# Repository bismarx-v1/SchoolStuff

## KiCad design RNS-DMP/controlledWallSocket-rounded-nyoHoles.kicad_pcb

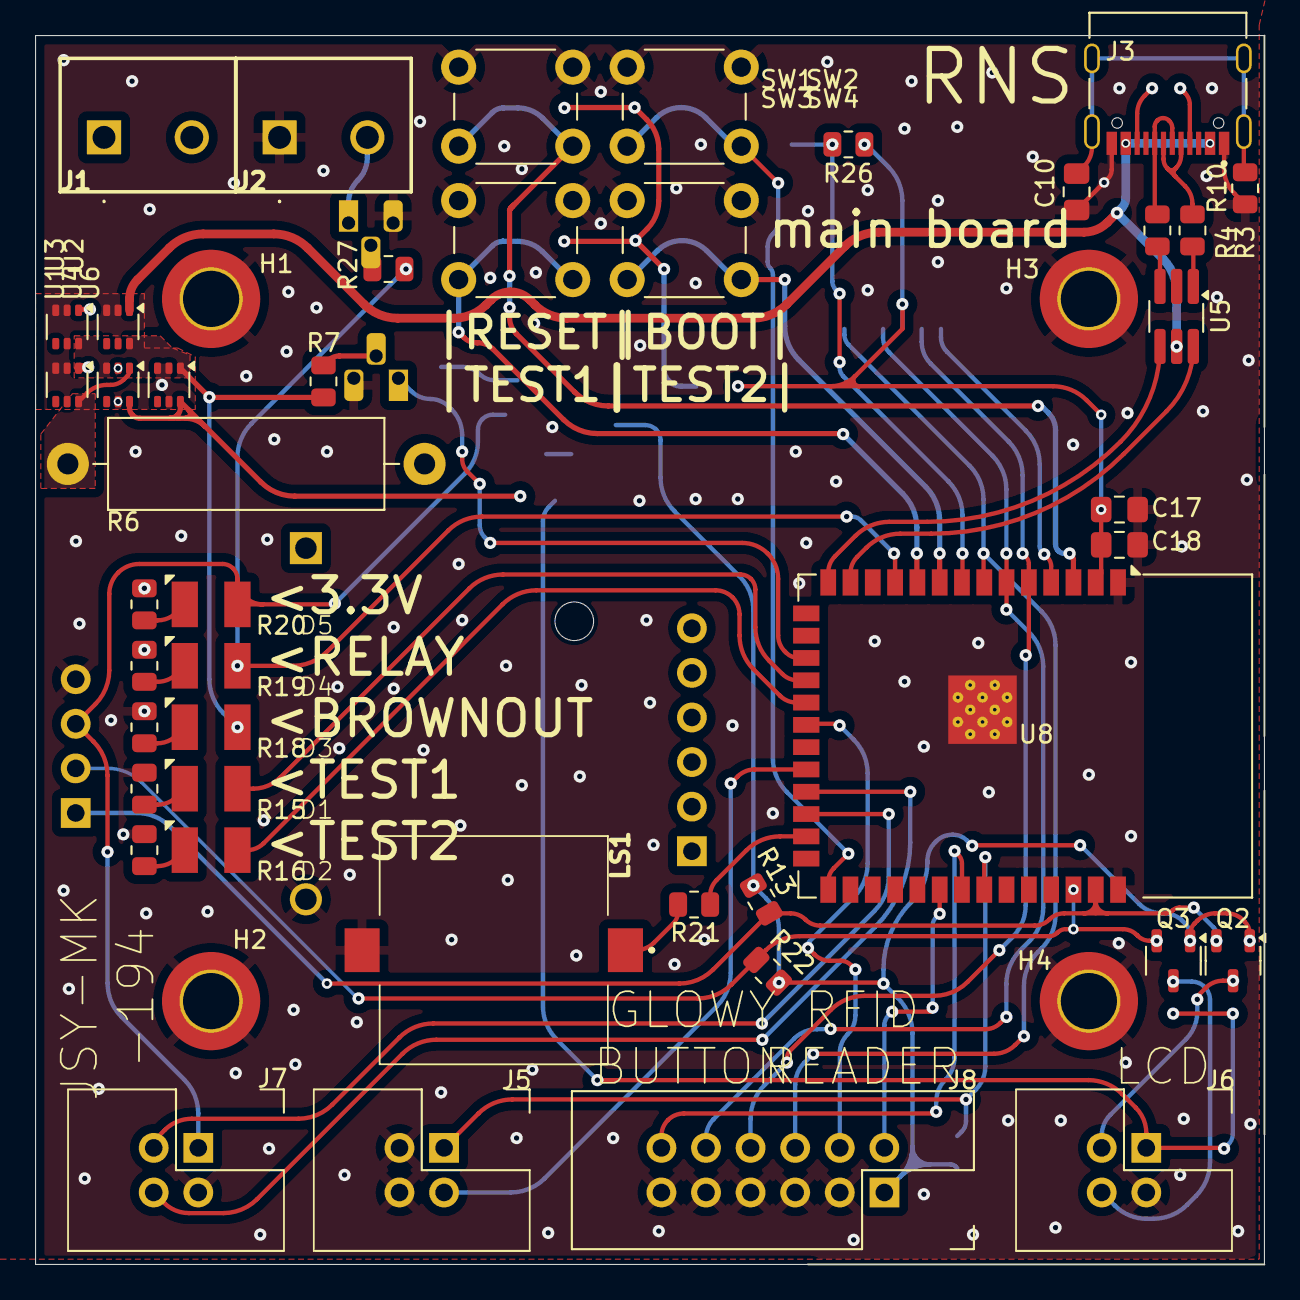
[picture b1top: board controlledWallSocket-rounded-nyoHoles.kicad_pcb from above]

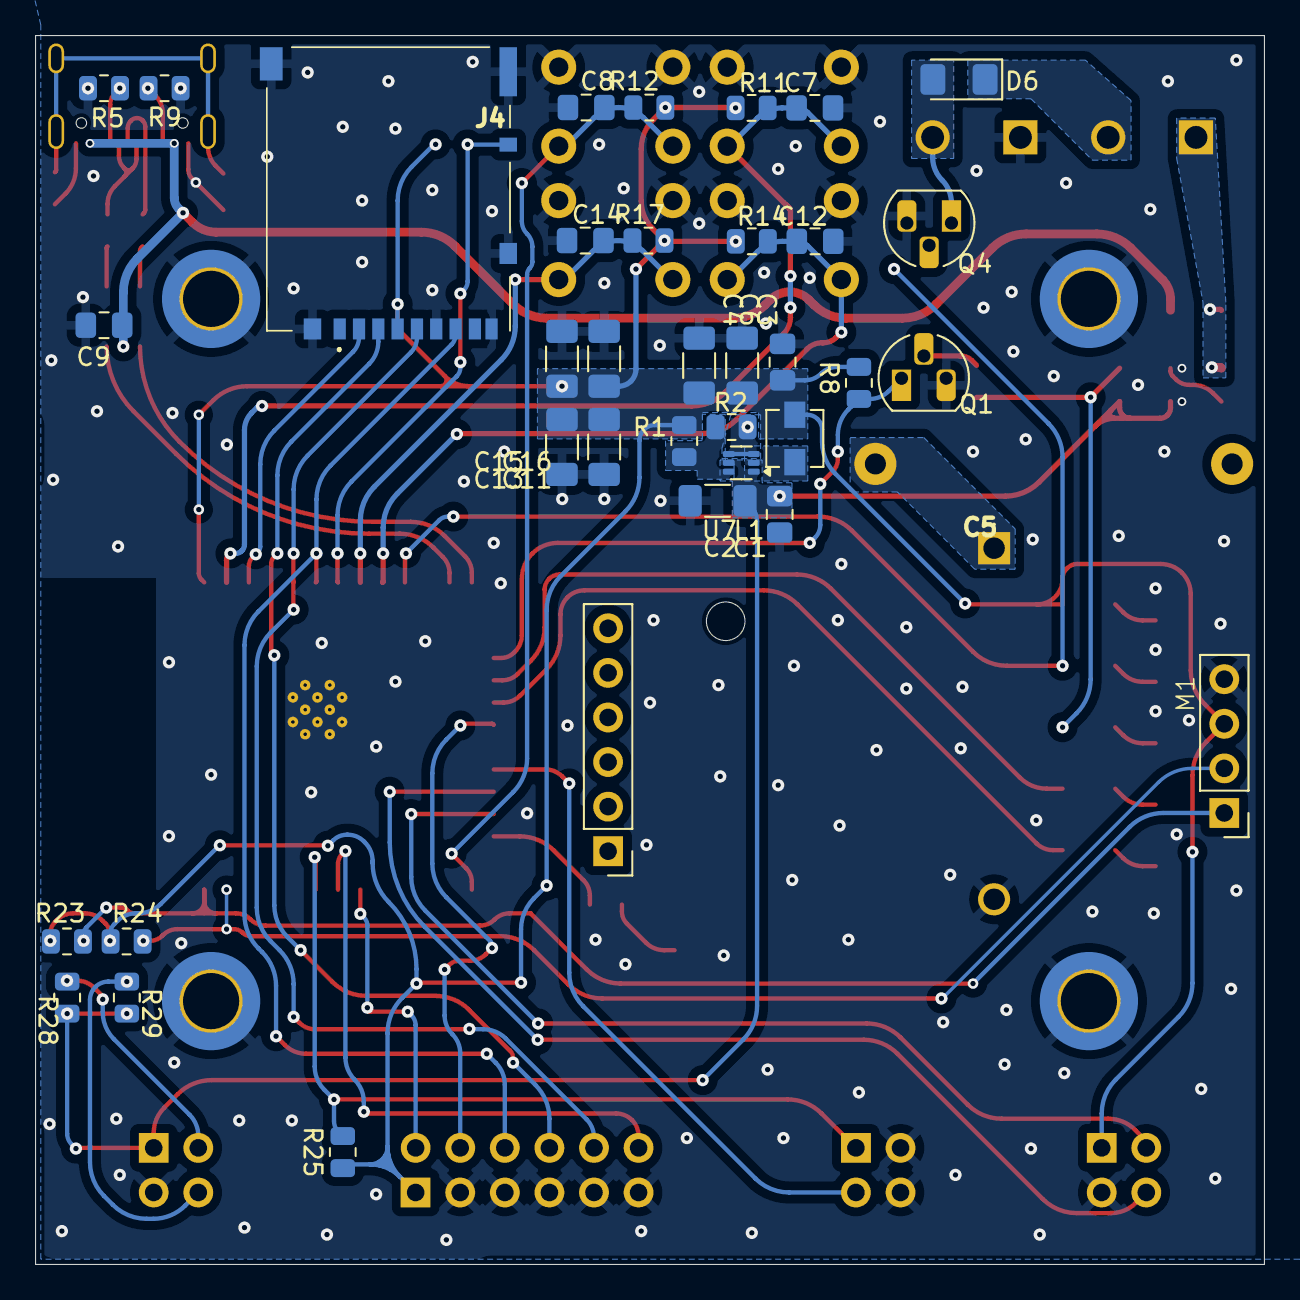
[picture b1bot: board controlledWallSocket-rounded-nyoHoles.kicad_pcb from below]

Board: 2 copper layers, 70.0 x 70.0 mm, 84 parts (36 on the bottom side), 54 nets.

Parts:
C1, C3, C7, C8, C9, C10, C12, C14, C18: 100nF; C_0805_2012Metric_Pad1.18x1.45mm_HandSolder
C2, C4, C6: 22u; C_1206_3216Metric_Pad1.33x1.80mm_HandSolder
C5: supercapacitor_KVR-5R0H105-R; supercapacitor_KVR5R0H105R
C11, C13, C15, C16: #; C_1206_3216Metric_Pad1.33x1.80mm_HandSolder
C17: 10uF; C_0805_2012Metric_Pad1.18x1.45mm_HandSolder
D1: pink; led3528
D2: violet; led3528
D3: blue; led3528
D4: green; led3528
D5: yellow; led3528
D6: SD1206S040S2R0; D_1206_3216Metric_Pad1.42x1.75mm_HandSolder
H1, H2, H3, H4: M3; MountingHole_3.2mm_M3_DIN965_Pad_TopBottom
J1, J2: screw term. 2x1 5mm; screwTerminal_DG3015002P1200AH
J3: USB_TypeC; usbC_HRO_TYPE-C-31-M-12
J4: sdCard_DM3AT-SF-PEJM5; sdCard_DM3ATSFPEJM5
J5, J6, J7: IDC 2x2; IDC 2x2 2.54
J8: IDC 6x2; IDC 6x2 2.54
L1: 1.5u; L_Vishay_IHLP-1212
LS1: buzzer_CPT-1625-80-SMT-TR; buzzer_CPT162580SMTTR
M1: RTC and EEPROM
Q1, Q4: bc337; TO-92_HandSolder
Q2, Q3: BSS138; SOT-23-3
R1: 45k; R_0805_2012Metric
R2, R8, R11, R12, R13, R14, R17, R22, R23, R24, R25, R26, R28, R29: 10k; R_0805_2012Metric
R3, R4: 15R; R_0805_2012Metric
R5, R9: 5.1k; R_0805_2012Metric
R6: 4.7R; R_Axial_DIN0516_L15.5mm_D5.0mm_P20.32mm_Horizontal
R7, R18, R27: 1k; R_0805_2012Metric
R10: 100k; R_0805_2012Metric
R15, R16, R19, R20: 220R; R_0805_2012Metric
R21: 0R; R_0805_2012Metric
SW1, SW2, SW3, SW4: SW_Push; SW_PUSH_6mm_H13mm
U1, U2, U3, U4, U6: LM66100Q; SOT-363_SC-70-6
U5: USBLC6-2SC6; TSOT-23-6_HandSoldering
U7: TPS565242DRLR; SOT-563
U8: ESP32-S3-WROOM-1

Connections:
+3.3V: C3.1, C4.1, C6.1, C11.1, C13.1, C15.1, C16.1, C17.1, C18.1, D5.2 (A), J4.4 (VDD), J7.1, J8.1, L1.2, M1.3 (VCC), Q2.1 (G), Q3.1 (G), R1.2, R8.1, R11.2, R12.2, R13.1, R14.2, R17.2, R22.1, R23.2, R24.2, R25.1, R26.1, U8.2 (3V3)
+5V: C1.1, C2.1, J6.1, R28.2, R29.2, U4.6 (VOUT), U6.6 (VOUT), U7.1 (VIN), U7.5 (EN)
+24V: D6.1 (K), J1.2
ESP_EN-btn_rst: C7.2, R11.1, SW1.2, U8.3 (EN)
ESP_IO0_BOOT-btn_boot: C8.2, R12.1, SW2.2, U8.27 (IO0)
ESP_IO04-btn_test1: C12.2, R14.1, SW3.2, U8.10 (IO17)
ESP_IO05-btn_test2: C14.2, R17.1, SW4.2, U8.9 (IO16)
ESP_IO6-RFID_IRQ: J8.4, U8.20 (IO12)
ESP_IO7-RFID_NRSTPD: J8.2, U8.32 (IO39)
ESP_IO8-SPI_CS_rfid: J8.12, U8.33 (IO40)
ESP_IO9-SPI_CS_sdCard: J4.2 (CD/DAT3), U8.4 (IO4)
ESP_IO10-SPI_MOSI: J4.3 (CMD), J8.8, U8.5 (IO5)
ESP_IO11-SPI_MISO: J4.7 (DAT0), J8.6, U8.7 (IO7)
ESP_IO12-SPI_CLK: J4.5 (CLK), J8.10, U8.6 (IO6)
ESP_IO13-UART_espRx: J7.2, U8.24 (IO47)
ESP_IO14-UART_espTx: J7.4, U8.23 (IO21)
ESP_IO15-IIC_SDA: M1.1 (SCL), Q2.2 (S), R13.2, R23.1, U8.39 (IO1)
ESP_IO16-IIC_SCL: M1.2 (SDA), Q3.2 (S), R22.2, R24.1, U8.38 (IO2)
ESP_IO38-relay_control: D4.2 (A), R27.1, U8.11 (IO18)
ESP_IO39-brownout_detected: Q1.1 (C), R8.2, U8.17 (IO9)
ESP_IO40-btnGlow_button: J5.1, R25.2, U8.34 (IO41)
ESP_IO41-btnGlow_LED: J5.3, U8.22 (IO14)
ESP_IO42-sdCardPresent: J4.MP4, R26.2, U8.8 (IO15)
ESP_IO47-led_test1: D1.2 (A), U8.18 (IO10)
ESP_IO48-led_test2: D2.2 (A), U8.19 (IO11)
ESP_IO#-buzzer: R21.2, U8.25 (IO48)
ESP_USB_D#-USB_MAIN_DN: U5.6, U8.13 (USB_D-)
ESP_USB_D#-USB_MAIN_DP: U5.4, U8.14 (USB_D+)
GND: C1.2, C2.2, C3.2, C4.2, C5.2 (-), C6.2, C7.1, C8.1, C9.2, C10.1, C11.2, C12.1, C13.2, C14.1, C15.2, C16.2, C17.2, C18.2, H1.1, H2.1, H3.1, H4.1, J2.1, J3.A1_B12 (GND), J3.B1_A12 (GND), J4.6 (VSS), J4.MP1, J4.MP2, J4.MP3, J4.MP5, J4.MP6, J5.2, J5.4, J6.3, J7.3, J8.3, J8.5, J8.7, J8.9, J8.11, LS1.2 (-), M1.4 (VSS), Q1.3 (E), Q4.3 (E), R2.1, R5.1, R9.1, R10.2, R15.2, R16.2, R18.2, R19.2, R20.2, SW1.1, SW2.1, SW3.1, SW4.1, U1.2 (GND), U1.3 (~CE), U1.5 (ST), U2.2 (GND), U2.3 (~CE), U2.5 (ST), U3.2 (GND), U3.3 (~CE), U3.5 (ST), U4.2 (GND), U4.5 (ST), U5.2, U6.2 (GND), U6.3 (~CE), U6.5 (ST), U7.3 (GND), U7.4 (AGND), U8.1 (GND), U8.40 (GND), U8.41 (GND)
IIC_5V_SDA: J6.2, Q2.3 (D), R28.1
IIC_5V_SLC: J6.4, Q3.3 (D), R29.1
unnamed: C5.1 (+), R6.1
unnamed: C10.2, J3.S1 (SHIELD), J3.S2 (SHIELD), J3.S3 (SHIELD), J3.S4 (SHIELD), R10.1
unnamed: D1.1 (K), R15.1
unnamed: D2.1 (K), R16.1
unnamed: D3.1 (K), R18.1
unnamed: D4.1 (K), R19.1
unnamed: D5.1 (K), R20.1
unnamed: J3.A5 (CC1), R5.2
unnamed: J3.B5 (CC2), R9.2
unnamed: LS1.1 (+), R21.1
unnamed: Q1.2 (B), R7.2
unnamed: Q4.2 (B), R27.2
unnamed: R3.2, U5.1
unnamed: R4.2, U5.3
unnamed: R6.2, U1.6 (VOUT), U4.1 (VIN)
unnamed: R1.1, R2.2, U7.6 (FB)
unnamed: L1.1, U7.2 (SW)
USB_MAIN_DN: J3.A7 (DN1), J3.B7 (DN2), R3.1
USB_MAIN_DP: J3.A6 (DP1), J3.B6 (DP2), R4.1
USB_MAIN_Vbus: C9.1, J3.A4_B9 (VBUS), J3.B4_A9 (VBUS), U2.1 (VIN), U5.5
raw_5V: J1.1, U1.1 (VIN), U3.1 (VIN)
relay_control: D6.2 (A), J2.2, Q4.1 (C)
statusLed_brownout_5V: D3.2 (A), R7.1, U2.6 (VOUT), U3.6 (VOUT), U4.3 (~CE), U6.1 (VIN)

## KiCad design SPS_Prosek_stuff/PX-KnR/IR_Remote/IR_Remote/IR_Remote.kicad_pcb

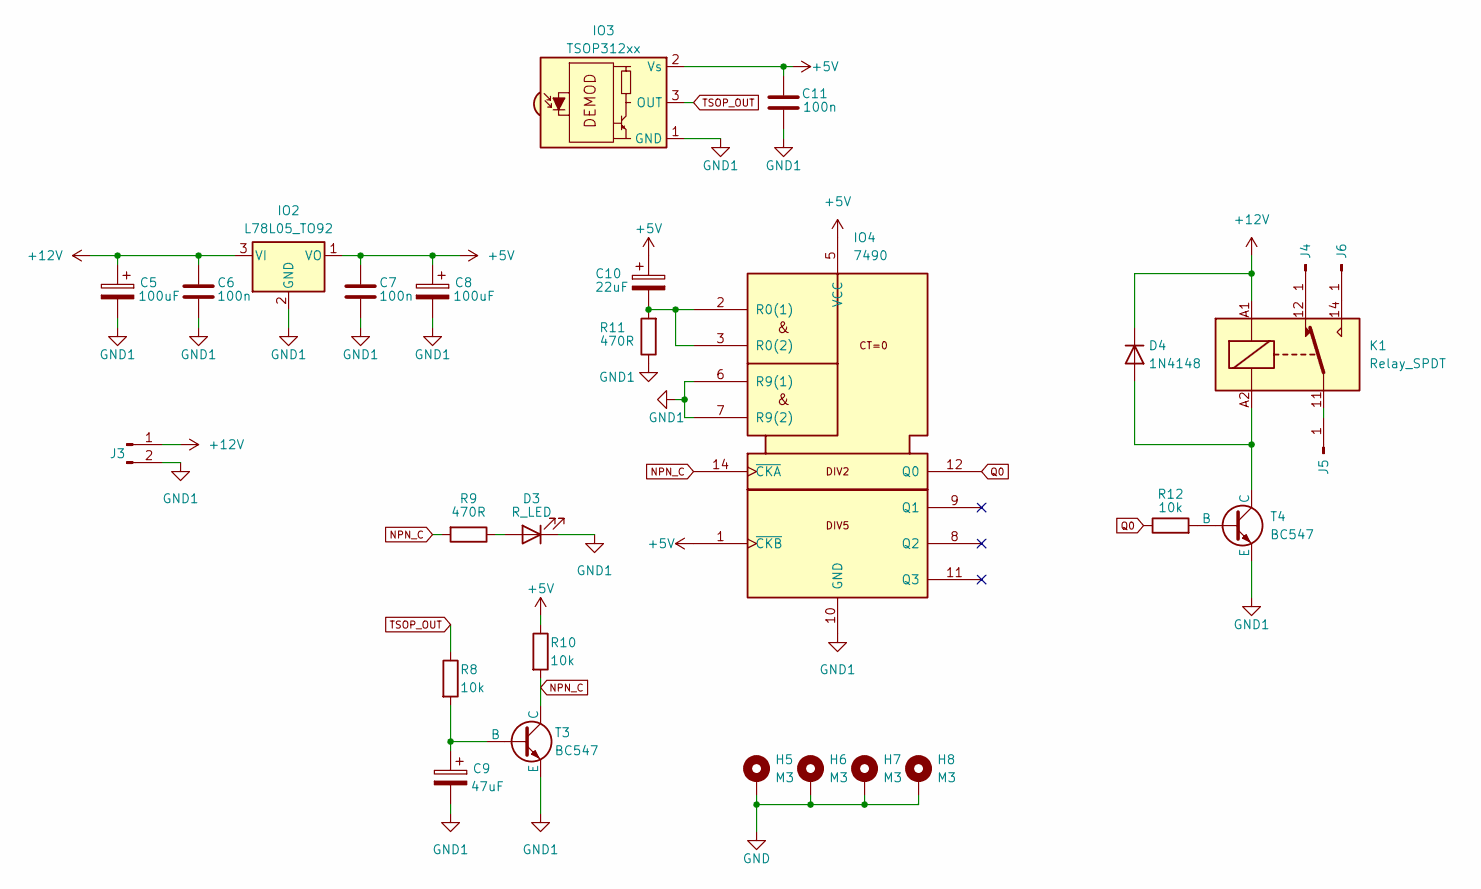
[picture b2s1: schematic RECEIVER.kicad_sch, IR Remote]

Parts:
C5, C8: 100uF; CP_Radial_D6.3mm_P2.50mm
C6, C7, C11: 100n; C_Disc_D4.3mm_W1.9mm_P5.00mm
C9: 47uF; CP_Radial_D6.3mm_P2.50mm
C10: 22uF; CP_Radial_D6.3mm_P2.50mm
D3: R_LED; LED_D5.0mm
D4: 1N4148; D_DO-35_SOD27_P7.62mm_Horizontal
H5, H6, H7, H8: M3; MountingHole_3.2mm_M3_ISO7380_Pad
IO2: L78L05_TO92; TO-92_Inline_Wide
IO3: TSOP312xx; Vishay_CAST-3Pin
IO4: 7490; DIP-14_W7.62mm
J3: Conn_01x02_Pin; PinHeader_1x02_P2.54mm_Vertical
J4, J5, J6: Conn_01x01_Pin; PinHeader_1x01_P2.54mm_Vertical
K1: Relay_SPDT; Relay_SPDT_Finder_36.11
R8, R10, R12: 10k; R_Axial_DIN0207_L6.3mm_D2.5mm_P10.16mm_Horizontal
R9, R11: 470R; R_Axial_DIN0207_L6.3mm_D2.5mm_P10.16mm_Horizontal
T3, T4: BC547; TO-92_Inline_Wide

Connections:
+5V: C7.2, C8.1, C10.1, C11.1, IO2.1 (VO), IO3.2 (Vs), IO4.1 (~CKB), IO4.5 (VCC), R10.1
+12V: C5.1, C6.2, D4.1 (K), IO2.3 (VI), J3.1, K1.A1
GND: H5.1, H6.1, H7.1, H8.1; also elsewhere on the board
GND1: C5.2, C6.1, C7.1, C8.2, C9.2, C11.2, D3.1 (K), IO2.2 (GND), IO3.1 (GND), IO4.6 (R9(1)), IO4.7 (R9(2)), IO4.10 (GND), J3.2, R11.1, T3.3 (E), T4.3 (E); also elsewhere on the board
NPN_C: IO4.14 (~CKA), R9.2, R10.2, T3.1 (C)
unnamed: D3.2 (A), R9.1
unnamed: D4.2 (A), K1.A2, T4.1 (C)
unnamed: C10.2, IO4.2 (R0(1)), IO4.3 (R0(2)), R11.2
unnamed: J4.1, K1.12
unnamed: J5.1, K1.11
unnamed: J6.1, K1.14
unnamed: C9.1, R8.2, T3.2 (B)
unnamed: R12.2, T4.2 (B)
Q0: IO4.12 (Q0), R12.1
TSOP_OUT: IO3.3 (OUT), R8.1

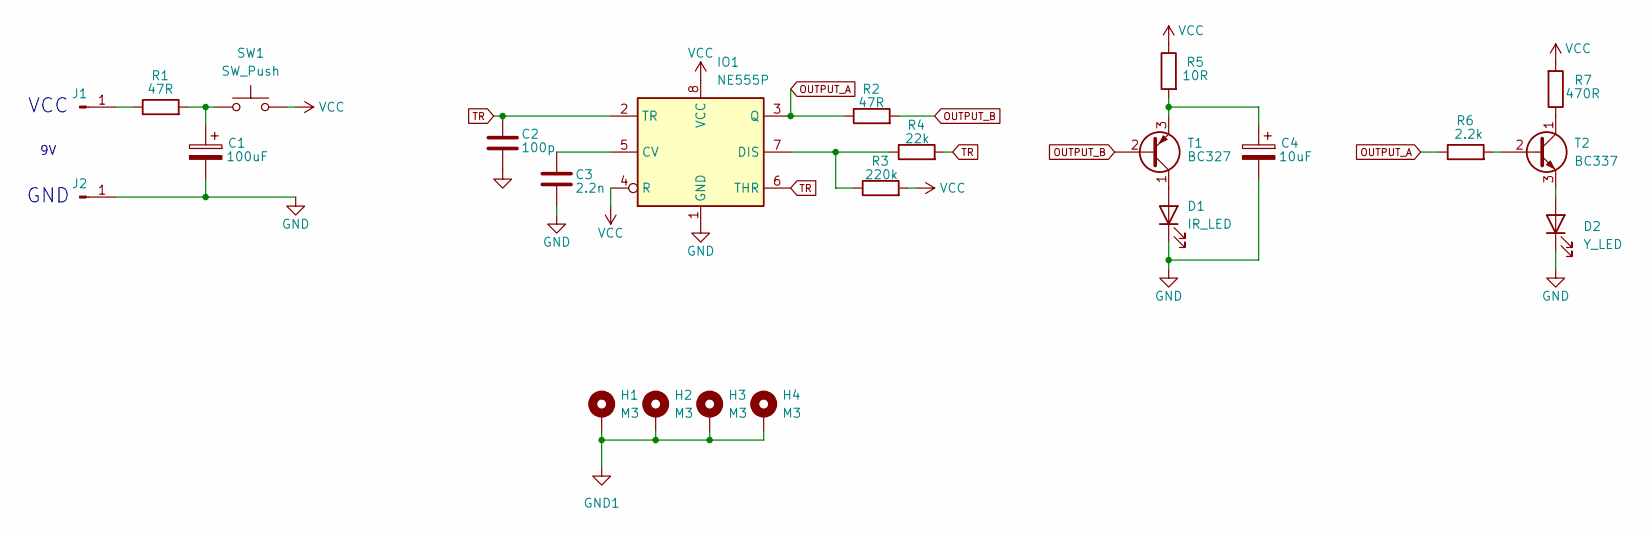
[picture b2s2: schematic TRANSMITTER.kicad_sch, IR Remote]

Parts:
C1: 100uF; CP_Radial_D6.3mm_P2.50mm
C2: 100p; C_Disc_D4.3mm_W1.9mm_P5.00mm
C3: 2.2n; C_Disc_D5.0mm_W2.5mm_P5.00mm
C4: 10uF; CP_Radial_D6.3mm_P2.50mm
D1: IR_LED; LED_D5.0mm_Horizontal_O1.27mm_Z3.0mm_Clear
D2: Y_LED; LED_D5.0mm
H1, H2, H3, H4: M3; MountingHole_3.2mm_M3_ISO7380_Pad
IO1: NE555P; DIP-8_W7.62mm
J1, J2: Conn_01x01_Pin; SolderWire-0.5sqmm_1x01_D0.9mm_OD2.3mm
R1, R2: 47R; R_Axial_DIN0207_L6.3mm_D2.5mm_P10.16mm_Horizontal
R3: 220k; R_Axial_DIN0207_L6.3mm_D2.5mm_P10.16mm_Horizontal
R4: 22k; R_Axial_DIN0207_L6.3mm_D2.5mm_P10.16mm_Horizontal
R5: 10R; R_Axial_DIN0207_L6.3mm_D2.5mm_P10.16mm_Horizontal
R6: 2.2k; R_Axial_DIN0207_L6.3mm_D2.5mm_P10.16mm_Horizontal
R7: 470R; R_Axial_DIN0207_L6.3mm_D2.5mm_P10.16mm_Horizontal
SW1: SW_Push; SW_PUSH_6mm_H5mm
T1: BC327; TO-92_Inline_Wide
T2: BC337; TO-92_Inline_Wide

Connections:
GND: C1.2, C2.1, C3.2, C4.2, D1.1 (K), D2.1 (K), IO1.1 (GND), J2.1; also elsewhere on the board
GND1: H1.1, H2.1, H3.1, H4.1; also elsewhere on the board
unnamed: C1.1, R1.2, SW1.1
unnamed: D1.2 (A), T1.1 (C)
unnamed: D2.2 (A), T2.3 (E)
unnamed: C3.1, IO1.5 (CV)
unnamed: IO1.7 (DIS), R3.1, R4.1
unnamed: J1.1, R1.1
unnamed: C4.1, R5.2, T1.3 (E)
unnamed: R6.2, T2.2 (B)
unnamed: R7.1, T2.1 (C)
OUTPUT_A: IO1.3 (Q), R2.1, R6.1
OUTPUT_B: R2.2, T1.2 (B)
TR: C2.2, IO1.2 (TR), IO1.6 (THR), R4.2
VCC: IO1.4 (R), IO1.8 (VCC), R3.2, R5.1, R7.2, SW1.2

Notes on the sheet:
GND
VCC

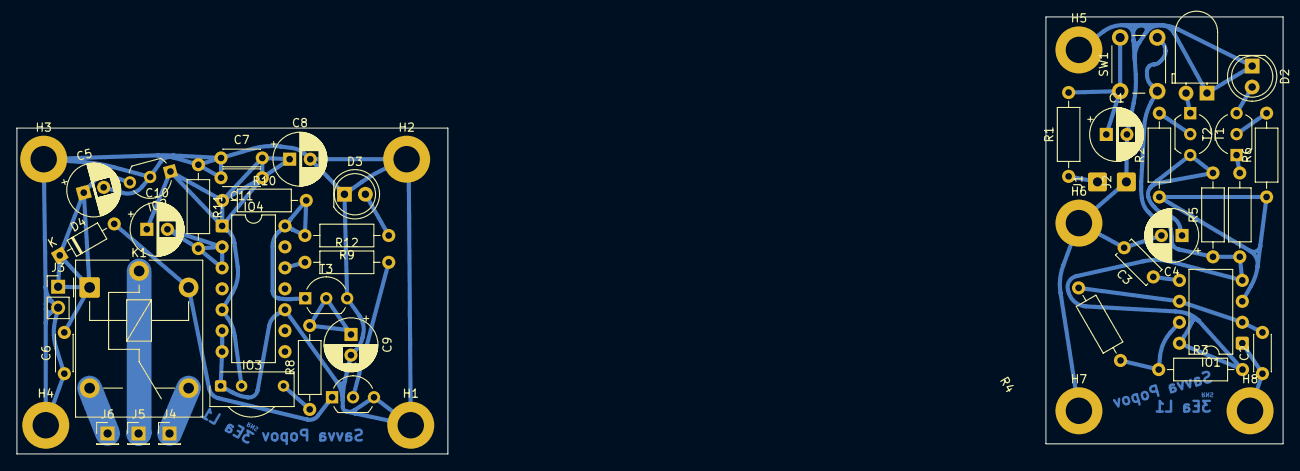
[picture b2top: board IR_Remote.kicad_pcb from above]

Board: 2 copper layers, 153.5 x 53.0 mm, 51 parts (0 on the bottom side), 28 nets.

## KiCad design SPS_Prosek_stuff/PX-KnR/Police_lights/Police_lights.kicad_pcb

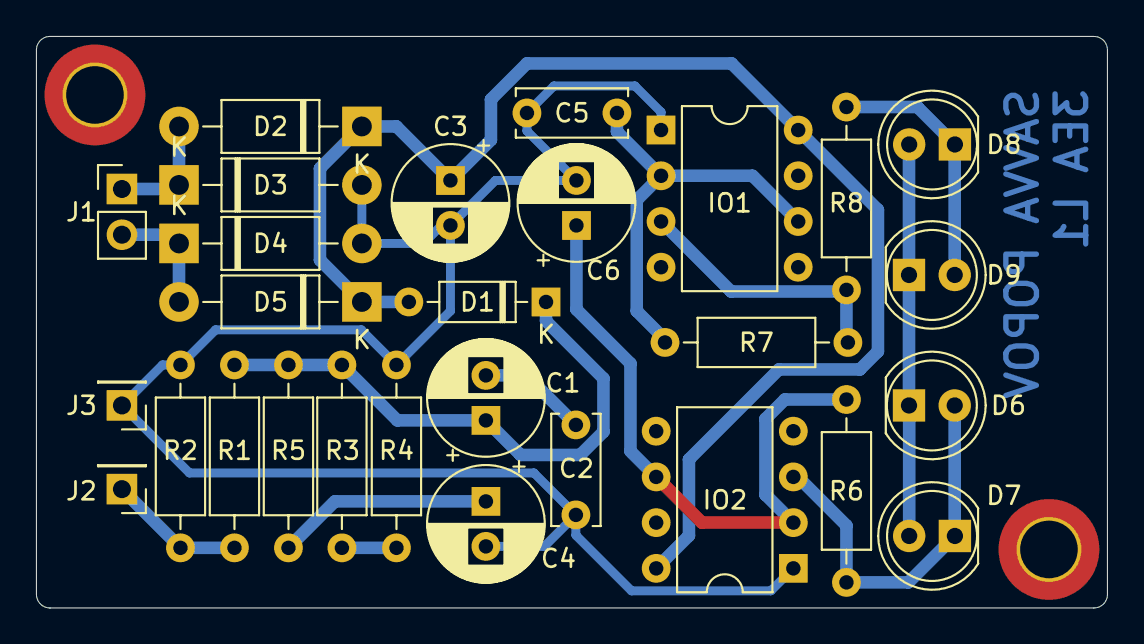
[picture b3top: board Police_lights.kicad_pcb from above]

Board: 2 copper layers, 59.5 x 31.8 mm, 30 parts (0 on the bottom side), 15 nets.

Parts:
C1, C4: 10uF/50V; CP_Radial_D6.3mm_P2.50mm
C2: 100pF; C_Disc_D6.0mm_W2.5mm_P5.00mm
C3: 100uF/16V; CP_Radial_D6.3mm_P2.50mm
C5: 100nF; C_Disc_D6.0mm_W2.5mm_P5.00mm
C6: 1uF/50V; CP_Radial_D6.3mm_P2.50mm
D1: 1N4148; D_DO-35_SOD27_P7.62mm_Horizontal
D2, D3, D4, D5: 1N4007; D_DO-41_SOD81_P10.16mm_Horizontal
D6, D7, D8, D9: LED; LED_D5.0mm_Clear
H1, H2: M3; MountingHole_3.2mm_M3_DIN965_Pad_TopBottom
IO1, IO2: NE555P; DIP-8_W7.62mm
J1: Conn_01x02_Pin; PinHeader_1x02_P2.54mm_Vertical
J2, J3: DC; PinHeader_1x01_P2.54mm_Vertical
R1: 15k; R_Axial_DIN0207_L6.3mm_D2.5mm_P10.16mm_Horizontal
R2: 2.2k; R_Axial_DIN0207_L6.3mm_D2.5mm_P10.16mm_Horizontal
R3, R4: 10k; R_Axial_DIN0207_L6.3mm_D2.5mm_P10.16mm_Horizontal
R5: 100R; R_Axial_DIN0207_L6.3mm_D2.5mm_P10.16mm_Horizontal
R6, R7: 1M; R_Axial_DIN0207_L6.3mm_D2.5mm_P10.16mm_Horizontal
R8: 470R; R_Axial_DIN0207_L6.3mm_D2.5mm_P10.16mm_Horizontal

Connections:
DIVIDER: J2.1, R1.1, R2.2
GND: C2.2, C3.2, C4.2, C5.2, C6.2, D3.2 (A), D4.2 (A), IO1.1 (GND), IO2.1 (GND), J3.1, R2.1, R4.1
unnamed: C1.2, C2.1
unnamed: C4.1, R5.1
unnamed: C1.1, D1.1 (K), R1.2, R3.2, R5.2
unnamed: D2.2 (A), D3.1 (K), J1.1
unnamed: D4.1 (K), D5.2 (A), J1.2
unnamed: D6.1 (K), D7.2 (A), D8.2 (A), D9.1 (K)
unnamed: D8.1 (K), D9.2 (A), R8.1
unnamed: R3.1, R4.2
Q_1: IO1.3 (Q), R7.1, R8.2
Q_2: D6.2 (A), D7.1 (K), IO2.3 (Q), R6.1
TR_1: C5.1, IO1.2 (TR), IO1.6 (THR), R7.2
TR_2: C6.1, IO2.2 (TR), IO2.6 (THR), R6.2
VCC: C3.1, D1.2 (A), D2.1 (K), D5.1 (K), IO1.8 (VCC), IO2.8 (VCC)

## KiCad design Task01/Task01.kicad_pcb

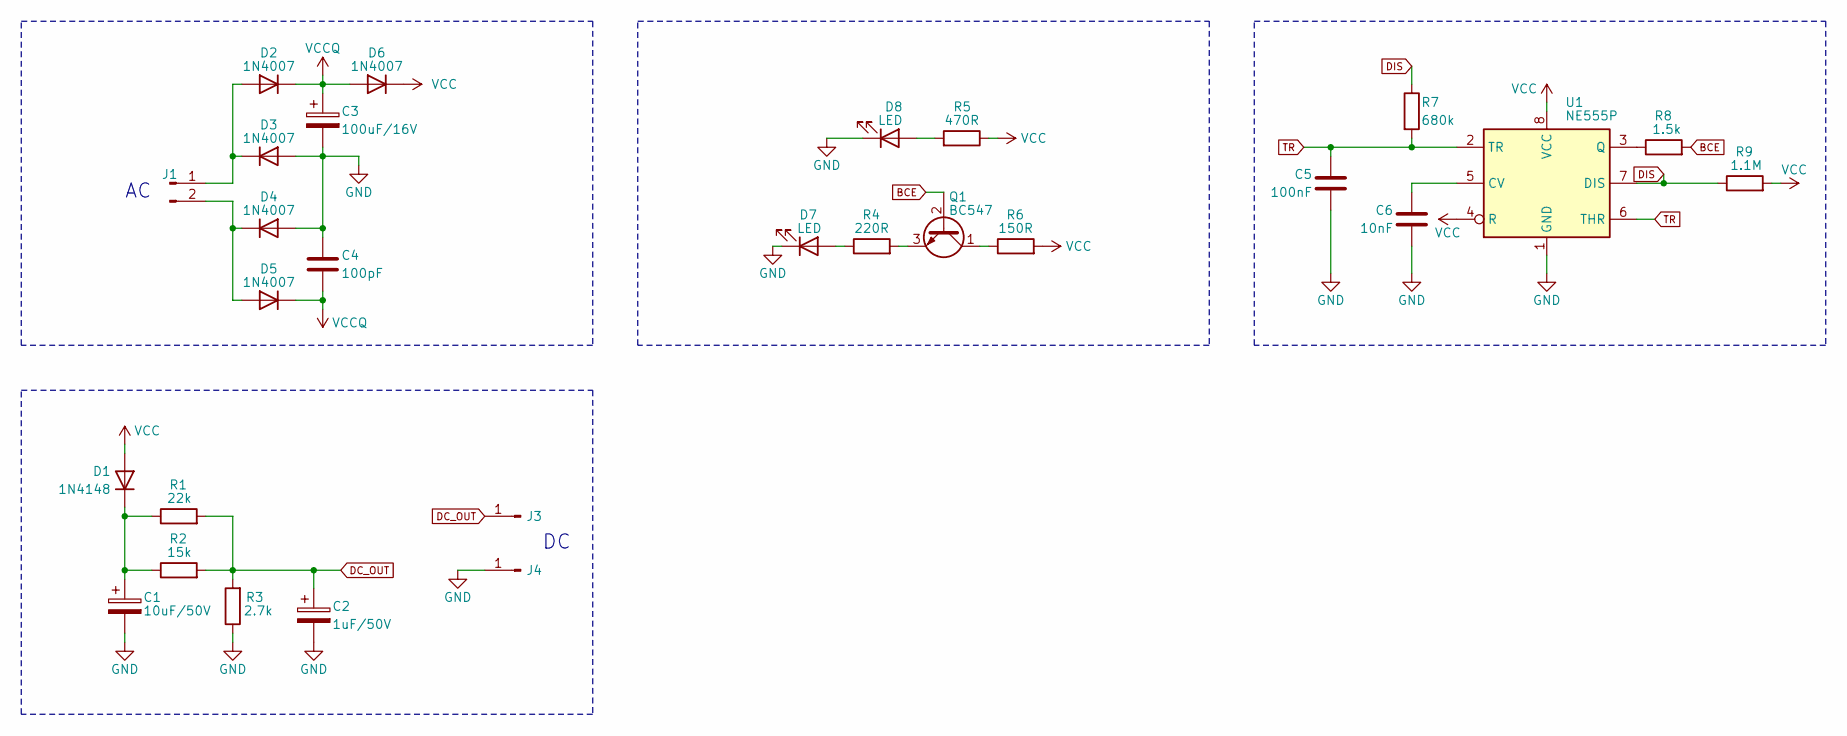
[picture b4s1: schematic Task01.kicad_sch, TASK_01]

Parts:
C1: 10uF/50V; CP_Radial_D6.3mm_P2.50mm
C2: 1uF/50V; CP_Radial_D6.3mm_P2.50mm
C3: 100uF/16V; CP_Radial_D6.3mm_P2.50mm
C4: 100pF; C_Disc_D6.0mm_W2.5mm_P5.00mm
C5: 100nF; C_Disc_D6.0mm_W2.5mm_P5.00mm
C6: 10nF; C_Disc_D6.0mm_W2.5mm_P5.00mm
D1: 1N4148; D_DO-35_SOD27_P7.62mm_Horizontal
D2, D3, D4, D5, D6: 1N4007; D_DO-41_SOD81_P10.16mm_Horizontal
D7, D8: LED; LED_D5.0mm_Clear
J1: Conn_01x02_Pin; PinHeader_1x02_P2.54mm_Vertical
J3, J4: DC; PinHeader_1x01_P2.54mm_Vertical
Q1: BC547; TO-92_Inline
R1: 22k; R_Axial_DIN0207_L6.3mm_D2.5mm_P10.16mm_Horizontal
R2: 15k; R_Axial_DIN0207_L6.3mm_D2.5mm_P10.16mm_Horizontal
R3: 2.7k; R_Axial_DIN0207_L6.3mm_D2.5mm_P10.16mm_Horizontal
R4: 220R; R_Axial_DIN0207_L6.3mm_D2.5mm_P10.16mm_Horizontal
R5: 470R; R_Axial_DIN0207_L6.3mm_D2.5mm_P10.16mm_Horizontal
R6: 150R; R_Axial_DIN0207_L6.3mm_D2.5mm_P10.16mm_Horizontal
R7: 680k; R_Axial_DIN0207_L6.3mm_D2.5mm_P10.16mm_Horizontal
R8: 1.5k; R_Axial_DIN0207_L6.3mm_D2.5mm_P10.16mm_Horizontal
R9: 1.1M; R_Axial_DIN0207_L6.3mm_D2.5mm_P10.16mm_Horizontal
U1: NE555P; DIP-8_W7.62mm

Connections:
BCE: Q1.2 (B), R8.2
DC_OUT: C2.1, J3.1, R1.2, R2.2, R3.2
DIS: R7.1, R9.1, U1.7 (DIS)
GND: C1.2, C2.2, C3.2, C4.1, C5.2, C6.2, D3.2 (A), D4.2 (A), D7.1 (K), D8.1 (K), J4.1, R3.1, U1.1 (GND)
unnamed: C1.1, D1.1 (K), R1.1, R2.1
unnamed: D2.2 (A), D3.1 (K), J1.1
unnamed: D4.1 (K), D5.2 (A), J1.2
unnamed: D7.2 (A), R4.1
unnamed: D8.2 (A), R5.2
unnamed: Q1.1 (C), R6.1
unnamed: Q1.3 (E), R4.2
unnamed: C6.1, U1.5 (CV)
unnamed: R8.1, U1.3 (Q)
TR: C5.1, R7.2, U1.2 (TR), U1.6 (THR)
VCC: D1.2 (A), D6.1 (K), R5.1, R6.2, R9.2, U1.4 (R), U1.8 (VCC)
VCCQ: C3.1, C4.2, D2.1 (K), D5.1 (K), D6.2 (A)

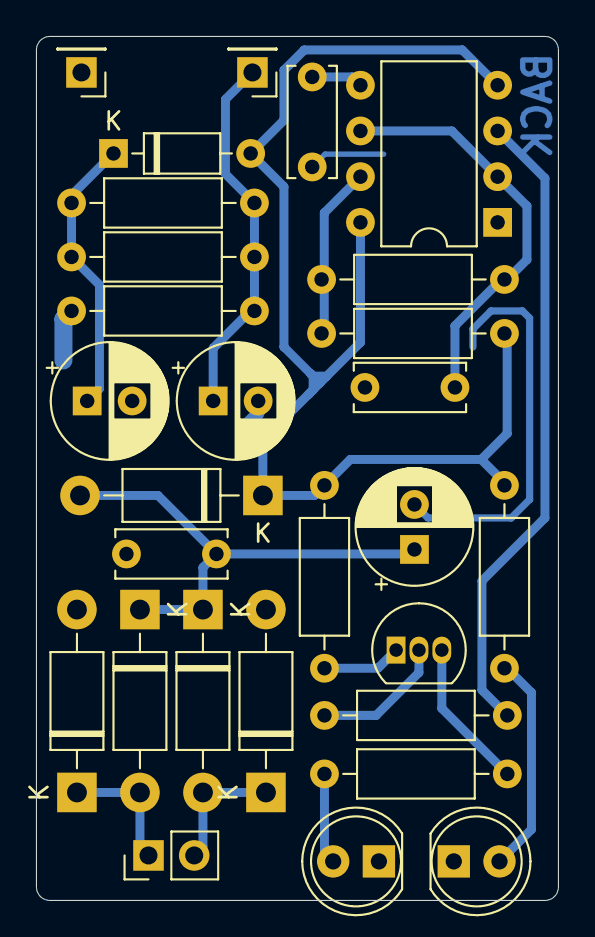
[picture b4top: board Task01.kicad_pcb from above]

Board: 2 copper layers, 29.0 x 48.0 mm, 28 parts (0 on the bottom side), 16 nets.

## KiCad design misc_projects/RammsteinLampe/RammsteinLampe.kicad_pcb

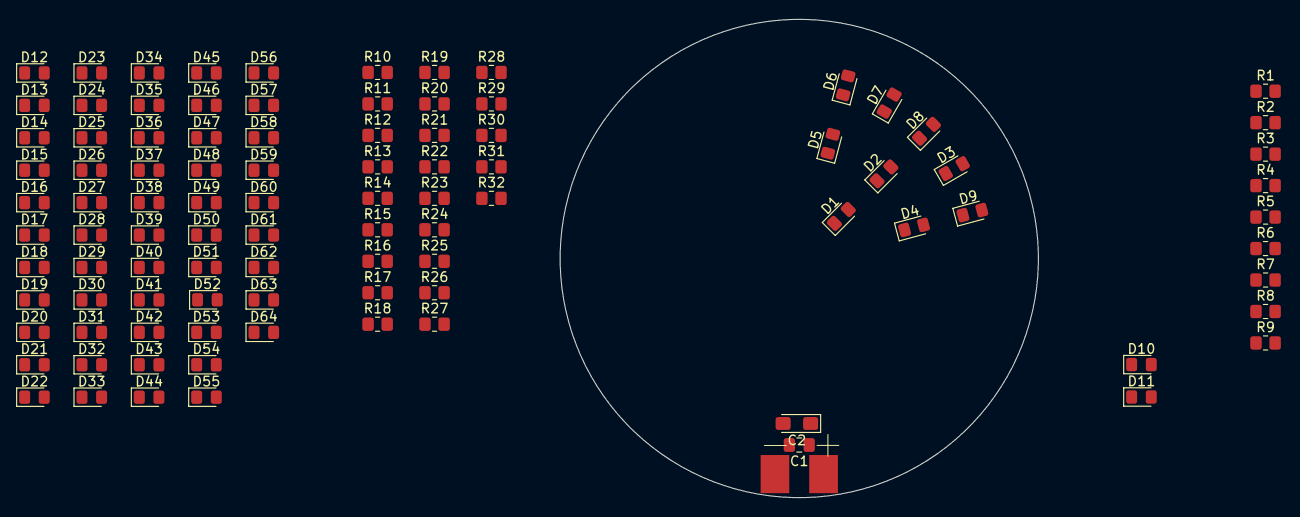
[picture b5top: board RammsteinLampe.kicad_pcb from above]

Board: 2 copper layers, 50.0 x 50.0 mm, 99 parts (0 on the bottom side), 34 nets, no tracks yet.

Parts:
C1: 100nF; C_0805_2012Metric_Pad1.18x1.45mm_HandSolder
C2: 10uF; CP_EIA-3216-18_Kemet-A_Pad1.58x1.35mm_HandSolder
D1, D2, D3, D4, D5, D6, D7, D8, D9, D10, D11, D12, D13, D14, D15, D16, D17, D18, D19, D20, D21, D22, D23, D24, D25, D26, D27, D28, D29, D30, D31, D32, D33, D34, D35, D36, D37, D38, D39, D40, D41, D42, D43, D44, D45, D46, D47, D48, D49, D50, D51, D52, D53, D54, D55, D56, D57, D58, D59, D60, D61, D62, D63, D64: R_LED; LED_0805_2012Metric_Pad1.15x1.40mm_HandSolder
J1: Conn_01x02_Pin; SOLDER_PADS
R1, R2, R3, R4, R5, R6, R7, R8, R9, R10, R11, R12, R13, R14, R15, R16, R17, R18, R19, R20, R21, R22, R23, R24, R25, R26, R27, R28, R29, R30, R31, R32: 220R; R_0805_2012Metric_Pad1.20x1.40mm_HandSolder

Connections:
+5V: C1.1, C2.1, J1.1, R1.1, R2.1, R3.1, R4.1, R5.1, R6.1, R7.1, R8.1, R9.1, R10.1, R11.1, R12.1, R13.1, R14.1, R15.1, R16.1, R17.1, R18.1, R19.1, R20.1, R21.1, R22.1, R23.1, R24.1, R25.1, R26.1, R27.1, R28.1, R29.1, R30.1, R31.1, R32.1
GND: C1.2, C2.2, D1.1 (K), D2.1 (K), D3.1 (K), D4.1 (K), D5.1 (K), D6.1 (K), D7.1 (K), D8.1 (K), D9.1 (K), D10.1 (K), D11.1 (K), D12.1 (K), D13.1 (K), D14.1 (K), D15.1 (K), D16.1 (K), D17.1 (K), D18.1 (K), D19.1 (K), D20.1 (K), D21.1 (K), D22.1 (K), D23.1 (K), D24.1 (K), D25.1 (K), D26.1 (K), D27.1 (K), D28.1 (K), D29.1 (K), D30.1 (K), D31.1 (K), D32.1 (K), D33.1 (K), D34.1 (K), D35.1 (K), D36.1 (K), D37.1 (K), D38.1 (K), D39.1 (K), D40.1 (K), D41.1 (K), D42.1 (K), D43.1 (K), D44.1 (K), D45.1 (K), D46.1 (K), D47.1 (K), D48.1 (K), D49.1 (K), D50.1 (K), D51.1 (K), D52.1 (K), D53.1 (K), D54.1 (K), D55.1 (K), D56.1 (K), D57.1 (K), D58.1 (K), D59.1 (K), D60.1 (K), D61.1 (K), D62.1 (K), D63.1 (K), D64.1 (K), J1.2
unnamed: D1.2 (A), D2.2 (A), R1.2
unnamed: D3.2 (A), D4.2 (A), R2.2
unnamed: D5.2 (A), D6.2 (A), R3.2
unnamed: D7.2 (A), D8.2 (A), R4.2
unnamed: D9.2 (A), D10.2 (A), R5.2
unnamed: D11.2 (A), D12.2 (A), R6.2
unnamed: D13.2 (A), D14.2 (A), R7.2
unnamed: D15.2 (A), D16.2 (A), R8.2
unnamed: D17.2 (A), D18.2 (A), R9.2
unnamed: D19.2 (A), D20.2 (A), R10.2
unnamed: D21.2 (A), D22.2 (A), R11.2
unnamed: D23.2 (A), D24.2 (A), R12.2
unnamed: D25.2 (A), D26.2 (A), R13.2
unnamed: D27.2 (A), D28.2 (A), R14.2
unnamed: D29.2 (A), D30.2 (A), R15.2
unnamed: D31.2 (A), D32.2 (A), R16.2
unnamed: D33.2 (A), D34.2 (A), R17.2
unnamed: D35.2 (A), D36.2 (A), R18.2
unnamed: D37.2 (A), D38.2 (A), R19.2
unnamed: D39.2 (A), D40.2 (A), R20.2
unnamed: D41.2 (A), D42.2 (A), R21.2
unnamed: D43.2 (A), D44.2 (A), R22.2
unnamed: D45.2 (A), D46.2 (A), R23.2
unnamed: D47.2 (A), D48.2 (A), R24.2
unnamed: D49.2 (A), D50.2 (A), R25.2
unnamed: D51.2 (A), D52.2 (A), R26.2
unnamed: D53.2 (A), D54.2 (A), R27.2
unnamed: D55.2 (A), D56.2 (A), R28.2
unnamed: D57.2 (A), D58.2 (A), R29.2
unnamed: D59.2 (A), D60.2 (A), R30.2
unnamed: D61.2 (A), D62.2 (A), R31.2
unnamed: D63.2 (A), D64.2 (A), R32.2
